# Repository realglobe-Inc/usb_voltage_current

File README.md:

# usb_voltage_current
Mac, LinuxマシンにUSBで接続できて追加ドライバ不要で値を読めるCO2センサ

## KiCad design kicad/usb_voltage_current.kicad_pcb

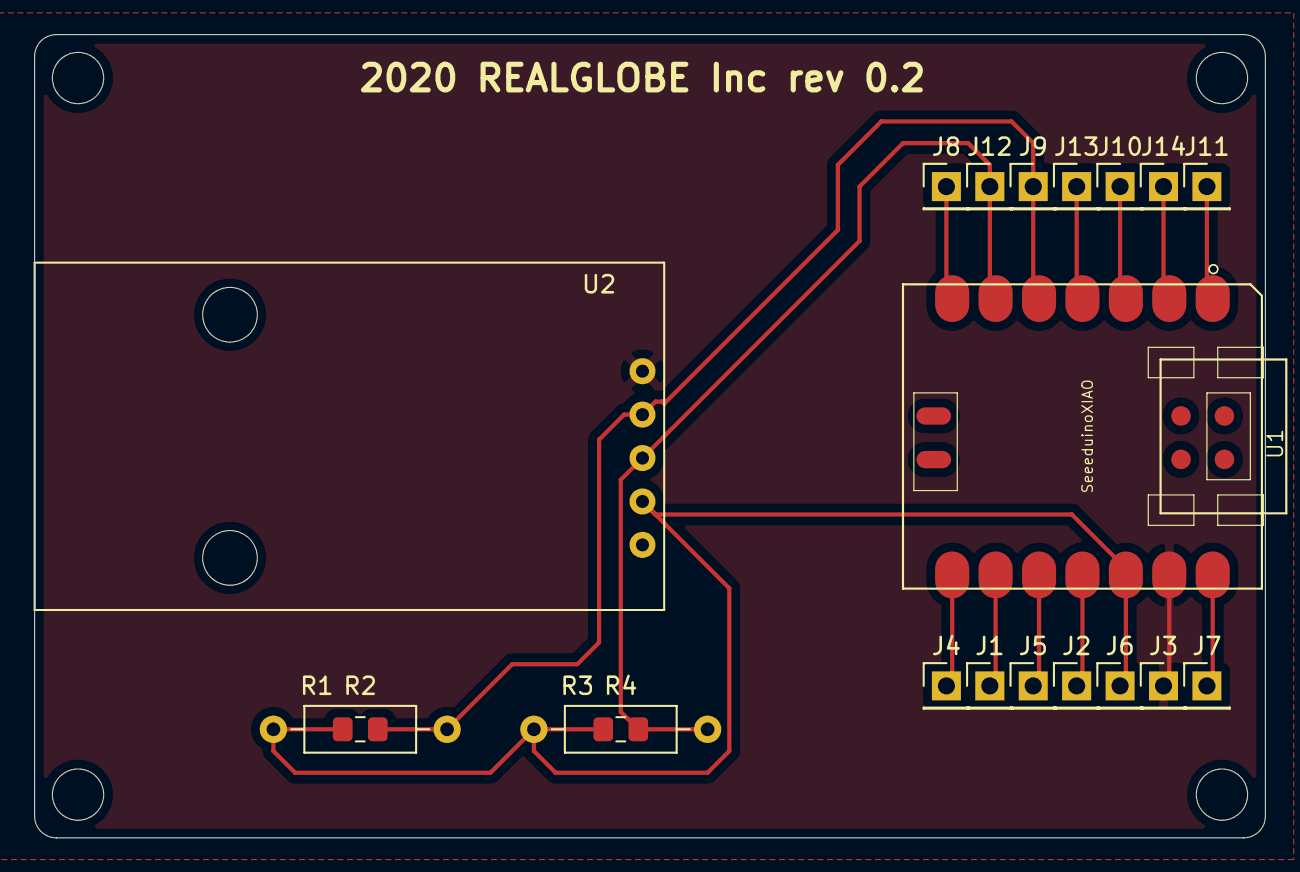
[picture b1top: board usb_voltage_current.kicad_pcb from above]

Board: 2 copper layers, 72.0 x 47.0 mm, 20 parts (0 on the bottom side), 14 nets.

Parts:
J1, J2, J3, J4, J5, J6, J7, J8, J9, J10, J11, J12, J13, J14: Conn_01x01; PinHeader_1x01_P2.54mm_Vertical
R1, R3: R; R_Axial_DIN0207_L6.3mm_D2.5mm_P10.16mm_Horizontal
R2, R4: R; R_0805_2012Metric_Pad1.15x1.40mm_HandSolder
U1: SeeeduinoXIAO; Seeeduino XIAO-MOUDLE14P-2.54-21X17.8MM
U2: INA226; ina226

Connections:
+3V3: J6.1, R1.1, R2.1, R3.1, R4.1, U1.12, U2.4
GND: J3.1, U1.13, U2.1
unnamed: J1.1, U1.9
unnamed: J2.1, U1.11
unnamed: J4.1, U1.8
unnamed: J5.1, U1.10
unnamed: J7.1, U1.14
unnamed: J8.1, U1.7
unnamed: J9.1, R1.2, R2.2, U1.5, U2.2
unnamed: J10.1, U1.3
unnamed: J11.1, U1.1
unnamed: J12.1, R3.2, R4.2, U1.6, U2.3
unnamed: J13.1, U1.4
unnamed: J14.1, U1.2

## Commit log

2020-07-31 回路作成
2020-07-31 配置配線終わり、DRCok
2020-07-31 REALGLOBEのシルクを追加
2020-09-08 プルアップ抵抗位置の修正とXIAOのVdd抜け修正
2020-09-08 AW修正
2020-09-08 基板シルクのリビジョンアップ
2020-09-11 初期化処理実装
2020-09-11 電圧電流リード処理を実装、電流はバグってる
2020-09-15 電流値がおかしくなる問題を修正
2020-09-15 電圧,電流,電力の実機動作確認済み
2020-09-15 メイン処理実装
2020-09-17 シリアル出力の電圧電流電力の表記を変えた
2020-09-17 シリアル出力にステータスをつけた
2020-09-25 シリアル出力の改行コードを変更した
2022-03-05 なんか変わった
2022-03-05 .DS_Storeを追加
2022-03-05 code-workspaceを追加
2022-03-05 署名を追加
